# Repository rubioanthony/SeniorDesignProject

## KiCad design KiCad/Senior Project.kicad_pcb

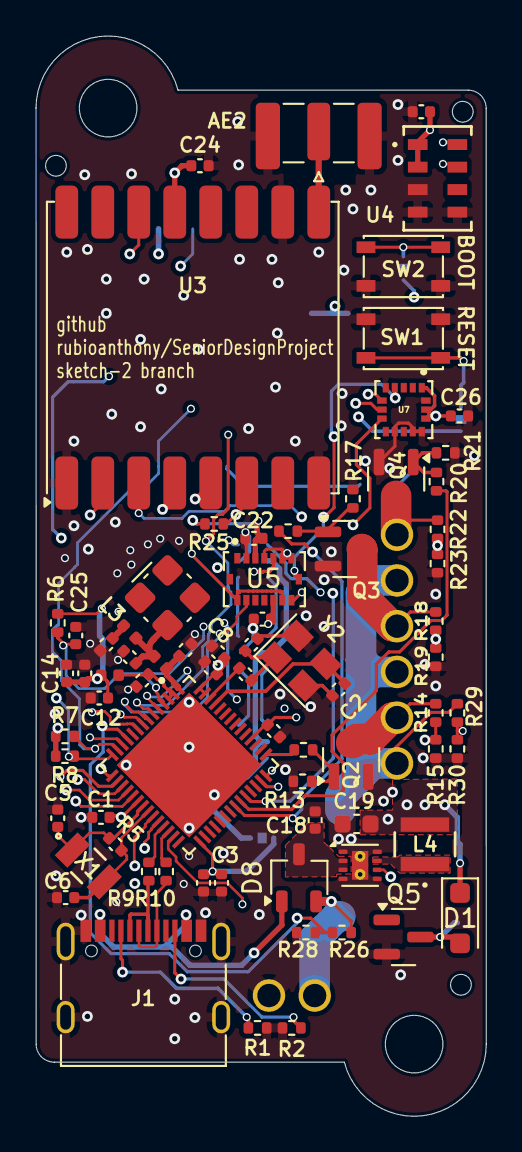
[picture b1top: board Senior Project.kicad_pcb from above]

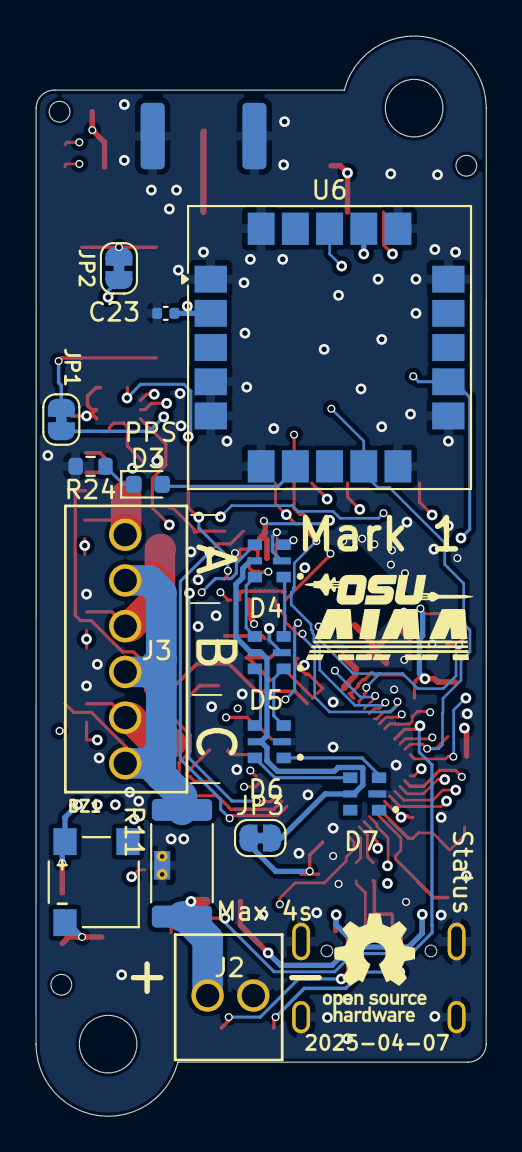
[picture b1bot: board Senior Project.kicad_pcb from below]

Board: 4 copper layers, 25.0 x 60.0 mm, 89 parts (15 on the bottom side), 65 nets.

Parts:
AE1: Antenna_Shield; Molex_47948-0001_2.4Ghz
AE2: Antenna_Shield; SMA_Samtec_SMA-J-P-H-ST-EM1_EdgeMount
BZ1: CMT-0525-75-SMT-TR; XDCR_CMT-0525-75-SMT-TR
C1, C3, C9, C11, C12, C15, C16, C17, C20, C21, C22, C23, C26: 100nF; C_0402_1005Metric
C2, C10: 15p; C_0402_1005Metric
C4: 10nF; C_0402_1005Metric
C5, C6: 20p; C_0402_1005Metric
C7, C8, C13, C24, C25: 1uF; C_0402_1005Metric
C14, C18: 10uF; C_0402_1005Metric
C19: 22uF; C_0603_1608Metric
D1: SM4007PL; D_SOD-123F
D3: LED; LED_0603_1608Metric
D4, D5, D6, D7: BB-2020BGR-TRB; LED_BB-2020BGR-TRB
D8: D_Dual_CommonCathode_AAK; TSOT-23
J1: USB_C_Receptacle_USB2.0_16P; USB_C_Receptacle_G-Switch_GT-USB-7010ASV
J2: Screw_Terminal_01x02; CONN_OSTVN02A150_OST
J3: Screw_Terminal_01x06; CONN_OSTVN06A150_OST
JP1, JP2, JP3: SolderJumper_2_Bridged; SolderJumper-2_P1.3mm_Bridged_RoundedPad1.0x1.5mm
L1, L2, L3: 2.0nH; L_0402_1005Metric
L4: 2.2uH; IND_TAIYO_NR3015_TAY
Q2, Q3, Q4, Q5: AO3400A; SOT-23
R1, R2: 5.1k; R_0402_1005Metric
R4: 24nH; C_0402_1005Metric
R5: TBD; C_0402_1005Metric
R6, R7, R8, R13, R17, R21: 10k; R_0402_1005Metric
R9, R10: 22; R_0402_1005Metric
R11: 1; R_2512_6332Metric
R12, R16, R20: 470; R_0402_1005Metric
R14, R18, R22, R26, R29: 510k; R_0402_1005Metric
R15, R19, R23, R28, R30: 33k; R_0402_1005Metric
R24: R_Small; R_0603_1608Metric
R25: 100k; R_0402_1005Metric
SW1, SW2: SW_Push; SW_SPST_PTS810
U1: ESP32-S3FH4R2; QFN40P700X700X90-57N
U2: TPS62162DSG; WSON-8-1EP_2x2mm_P0.5mm_EP0.9x1.6mm_ThermalVias
U3: RFM95W-868S2; HOPERF_RFM9XW_SMD
U4: MS560702BA03-50; SON8_MS5611_TEC
U5: BMI088; PQFN50P450X300X100-16N
U6: SAM-M10Q; ublox_SAM-M8Q
U7: H3LIS200DLTR; PQFN50P300X300X100-16N
X1: FC-135 32.7680KA-A5; XTAL_FC-135_EPS
Y2: Crystal_GND23; Crystal_SMD_3225-4Pin_3.2x2.5mm

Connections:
+3V3: BZ1.1 (+), C1.1, C3.1, C4.1, C7.1, C8.1, C9.1, C12.1, C13.1, C14.1, C19.1, C20.1, C21.1, C22.1, C23.2, C24.1, C26.1, D1.1 (K), JP3.1 (A), L1.2, L4.2, R6.1, R7.1, R8.1, R25.1, U1.20 (VDD3P3_RTC), U1.29 (VDD_SPI), U1.46 (VDD3P3_CPU), U1.55 (VDDA), U1.56 (VDDA__1), U2.6 (VOS), U3.13 (3.3V), U4.1 (VDD), U4.2 (PS), U5.3 (VDD), U5.11 (VDDIO), U6.2 (VCC_IO), U6.17 (VCC), U7.1 (VDD_IO), U7.14 (VDD), U7.15 (VDD__1)
+BATT: D8.2 (A), J2.2, R11.1, R26.1
/BATTERY_SENSE: R26.2, R28.1, U1.11 (GPIO6)
/BOOT: JP2.2 (B), U1.5 (GPIO0)
/CURRENT_SENSE: R29.2, R30.1, U1.12 (GPIO7)
/FSPICLK: U1.17 (GPIO12), U3.4 (SCK), U5.8 (SCL/SCK), U7.4 (SCL/SPC)
/FSPICS0: U1.15 (GPIO10), U3.5 (NSS)
/FSPID: U1.16 (GPIO11), U3.3 (MOSI), U5.9 (SDA/SDI), U7.6 (SDA/SDI/SDO)
/FSPIQ: U1.18 (GPIO13), U3.2 (MISO), U5.10 (SDO2), U5.15 (SDO1), U7.7 (SDO/SA0)
/GPS_Reset: U1.8 (GPIO3), U6.18 (~RESET)
/Interrupt: U1.6 (GPIO1), U3.14 (DIO0)
/LED_CLK: D4.4 (CI), U1.42 (GPIO37)
/LED_D: D4.3 (DI), U1.41 (GPIO36)
/PowerReg/VUSB: D8.1 (A), J1.A4 (VBUS), J1.A9 (VBUS), J1.B4 (VBUS), J1.B9 (VBUS)
/Pyro Channel1/Pyro Pin: J3.2, Q2.3 (D), R14.1
/Pyro Channel2/Pyro Pin: J3.4, Q3.3 (D), R18.1
/Pyro Channel3/Pyro Pin: J3.6, Q4.3 (D), R22.1
/Pyro GPIO 1: R12.1, U1.43 (GPIO38)
/Pyro GPIO 2: R16.1, U1.36 (GPIO48/SPICLK_N)
/Pyro GPIO 3: R20.1, U1.37 (GPIO47/SPICLK_P)
/RADIO_RST: R25.2, U1.9 (GPIO4), U3.6 (RESET)
/SCL: R8.2, U1.14 (GPIO9), U4.8 (SCLK), U6.12 (SCL)
/SDA: R7.2, U1.13 (GPIO8), U4.7 (SDI/SDA), U6.9 (SDA)
/Sense 1: R14.2, R15.1, U1.19 (GPIO14)
/Sense 2: R18.2, R19.1, U1.23 (GPIO17)
/Sense 3: R22.2, R23.1, U1.24 (GPIO18)
/USB_D+: J1.A6 (D+), J1.B6 (D+), R10.2
/USB_D-: J1.A7 (D-), J1.B7 (D-), R9.1
/WiFi Antenna/LNA_IN: C15.1, L2.1, U1.1 (LNA_IN)
/~ACCELEROMETER_CS: U1.7 (GPIO2), U5.14 (CSB1)
/~GYRO_CS: U1.27 (GPIO21), U5.5 (CSB2)
/~HIGH_G_CS: U1.38 (GPIO33), U7.8 (CS)
/~RESET: C25.1, JP1.2 (B), R6.2, U1.4 (CHIP_PU)
GND: AE2.2 (Shield), C1.2, C2.1, C3.2, C4.2, C5.2, C6.2, C7.2, C8.2, C9.2, C10.1, C11.2, C12.2, C13.2, C14.2, C15.2, C16.2, C17.2, C18.2, C19.2, C20.2, C21.2, C22.2, C23.1, C24.2, C25.2, C26.2, D4.2 (GND), D5.2 (GND), D6.2 (GND), D7.2 (GND), J1.A1 (GND), J1.A12 (GND), J1.B1 (GND), J1.B12 (GND), J1.S1 (SHIELD), J2.1, Q2.2 (S), Q3.2 (S), Q4.2 (S), Q5.2 (S), R1.2, R2.2, R13.2, R15.2, R17.2, R19.2, R21.2, R23.2, R24.2, R28.2, R30.2, SW1.1, SW2.1, U1.57 (GND), U2.1 (PGND), U2.4 (AGND), U2.5 (FB), U2.8 (PG), U2.9 (PAD), U3.1 (GND), U3.8 (GND), U3.10 (GND), U4.3 (GND), U4.4 (~CSB), U4.5 (~CSB__1), U5.2 (NC), U5.4 (GNDA), U5.6 (GNDIO), U5.7 (PS), U6.1 (GND), U6.4 (GND), U6.5 (GND), U6.6 (GND), U6.10 (GND), U6.11 (GND), U6.15 (GND), U6.16 (GND), U6.20 (GND), U7.5 (GND), U7.10 (GND__1), U7.12 (GND__2), U7.13 (GND__3), U7.16 (GND__4), Y2.2, Y2.4
unnamed: AE1.1 (A), C16.1, L2.2, L3.1
unnamed: AE2.1 (A), U3.9 (ANT)
unnamed: BZ1.2 (-), D1.2 (A), Q5.3 (D)
unnamed: C10.2, R4.2, Y2.1
unnamed: C17.1, L3.2
unnamed: D3.2 (A), U6.7 (TIMEPULSE)
unnamed: D3.1 (K), R24.1
unnamed: D4.6 (CO), D5.4 (CI)
unnamed: D4.1 (DO), D5.3 (DI)
unnamed: D4.5 (VCC), D5.5 (VCC), D6.5 (VCC), D7.5 (VCC), JP3.2 (B)
unnamed: D5.6 (CO), D6.4 (CI)
unnamed: D5.1 (DO), D6.3 (DI)
unnamed: D6.6 (CO), D7.4 (CI)
unnamed: D6.1 (DO), D7.3 (DI)
unnamed: C18.1, D8.3 (K), U2.2 (VIN), U2.3 (EN)
unnamed: J1.A5 (CC1), R1.1
unnamed: J1.B5 (CC2), R2.1
unnamed: J3.1, J3.3, J3.5, R11.2, R29.1
unnamed: JP1.1 (A), SW1.2
unnamed: JP2.1 (A), SW2.2
unnamed: Q2.1 (G), R12.2, R13.1
unnamed: Q3.1 (G), R16.2, R17.1
unnamed: Q4.1 (G), R20.2, R21.1
unnamed: R9.2, U1.25 (GPIO19)
unnamed: R10.1, U1.26 (GPIO20)
unnamed: C11.1, L1.1, U1.2 (VDD3P3), U1.3 (VDD3P3__1)
unnamed: C6.1, R5.2, U1.22 (XTAL_32K_N), X1.2
unnamed: C5.1, R5.1, U1.21 (XTAL_32K_P), X1.1
unnamed: C2.2, U1.53 (XTAL_N), Y2.3
unnamed: R4.1, U1.54 (XTAL_P)
unnamed: L4.1, U2.7 (SW)

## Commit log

2025-01-26 initial
2025-02-23 Updated sensor block code
2025-03-02 Create RadioFiles
2025-03-02 Rename Example Wiring for Radio.png to Radio/Example Wiring for Radio.png
2025-03-03 Rename Radio/CON-SMA-EDGE-S.kicad_sym to Radio/sma_connector/CON-SMA-EDGE-S.kicad_sym
2025-03-03 Rename Radio/RFSOLUTIONS_CON-SMA-EDGE-S.kicad_mod to Radio/sma_connector/RFSOLUTIONS_CON-SMA-EDGE-S.kicad_mod
2025-03-13 Create Sensors
2025-03-13 Added Microcontroller + Initial Documentation
2025-03-13 Updated base file and added power reg + pyrochannel to main file
2025-03-13 Added the Radio
2025-03-13 Added Sensors block
2025-03-13 last pieces of stuff before new stuff can be added
2025-03-13 Added a screw terminal
2025-03-13 New GPS Module
2025-03-13 add cache files to ignore
2025-03-13 more aggressive matching
2025-03-13 very rough sketch layout
2025-03-13 redo power regulator area
2025-03-14 Reset all annotationss
2025-03-14 Updated several footprints
2025-03-14 All footprints placed
2025-03-14 Added Pyrochannels
2025-03-14 Layout started
2025-03-28 Added wiring for SPI
2025-03-28 I2C connections
2025-03-28 Pin adjust
2025-03-28 Layout updated. Very little left to do.
2025-03-31 saving old changes
2025-03-31 Added a diode to prevent reverse current issues
2025-03-31 Fixed some drc errors and pyro wiring
2025-03-31 DRC error fixes
2025-03-31 ERC fixes
2025-04-01 Removed traces, moved all comps to top
2025-04-01 New attempt at layout
2025-04-01 fix diode
2025-04-01 Added edge cuts for board
2025-04-01 Placement fixes
2025-04-01 Sensor placement, I2C pullup resistors, other placement changes.
2025-04-02 Finished initial placement
2025-04-02 Added power plane
2025-04-03 Added ground plane
2025-04-03 Small changes, few routes, need to plan for GPS fixes
2025-04-03 GPS 1 cm space
2025-04-03 did I really just do the whole thing in one commit
2025-04-03 Routing, placement
2025-04-04 Routing, schematic fixes, and minor placement changes.
2025-04-04 tighten up layout, swap out USB connector
2025-04-04 DRC rules are wrong, working on silkscreen
2025-04-04 Added ground support and 3.3 V via's
2025-04-05 Did some symbol changes, need to add more
2025-04-05 Added Diodes and did some routing
2025-04-05 Added filled zone for power regulation layout
2025-04-06 Routing
2025-04-06 Routing updates
2025-04-06 Made some local changes
2025-04-06 Added power routing moved usb, and routed a couple signals to radio
2025-04-06 Added power routing moved usb, and more routing
2025-04-06 Scap
2025-04-06 Removed micrcontroller
2025-04-06 Added some basic pin outs
2025-04-06 Added pushbuttons and power coupling
2025-04-06 Added jtag interface
2025-04-07 Finished base schematic and pin connections, need to add test pins
2025-04-07 ERC fixes and assigned footprints
2025-04-07 More footprints assigned
2025-04-07 More footprints
2025-04-07 Footprints
2025-04-07 Routing and placement
2025-04-07 More routing
2025-04-08 DRC issues, only a few signals left to be routed
2025-04-08 all DRC error fixed other than hole clearence issue, Only radio connection left to route
2025-04-08 all DRC error fixed other than hole clearence issue, Only radio connection left to route v2
2025-04-08 Fixes based on comments, entered design constraints
2025-04-09 Added design constraints and fixed some routing
2025-04-09 placeholder
2025-04-09 Max's feedback taken into account, have to add RF trace
2025-04-09 No DRC errors, radio atenna trace routed, waiting for feedback
2025-04-09 Silkscreen overlap fixes
2025-04-09 Minor fixes
2025-04-10 Switched to 2 layer board
2025-04-11 Major routing changes, back copper now 3V3 instead of ground, utilized back traces more.
2025-04-11 fixed all drc errors, adjusted routing and added ground plane
2025-04-23 fixed a couple issues
2025-04-25 Barometer schematic fix, JST connector, and few other fixes
2025-04-25 Back silkscreen text added
2025-04-25 add spot for high G accelerometer
2025-04-25 Switch added, LCSC table, other changes.
2025-04-25 Switch added to PCB
2025-04-26 Footprints added and small changes
2025-04-26 Final board design sent to OshPark
2025-04-26 add LEDs, OSU AIAA logo
2025-05-08 Added support for safe board and config pio proj
2025-05-08 added some stuff needed from Max's code
2025-05-08 added note have to initalize I2C for lsm6
2025-05-09 Adjusting code to fit safe board
2025-05-09 most recent code changes
2025-05-10 working radio and barometer code added
2025-05-11 Working radio, imu, and barometer code
2025-05-11 gps testing
2025-05-13 Added comments to code
2025-05-23 switch to double diode and add beeper
